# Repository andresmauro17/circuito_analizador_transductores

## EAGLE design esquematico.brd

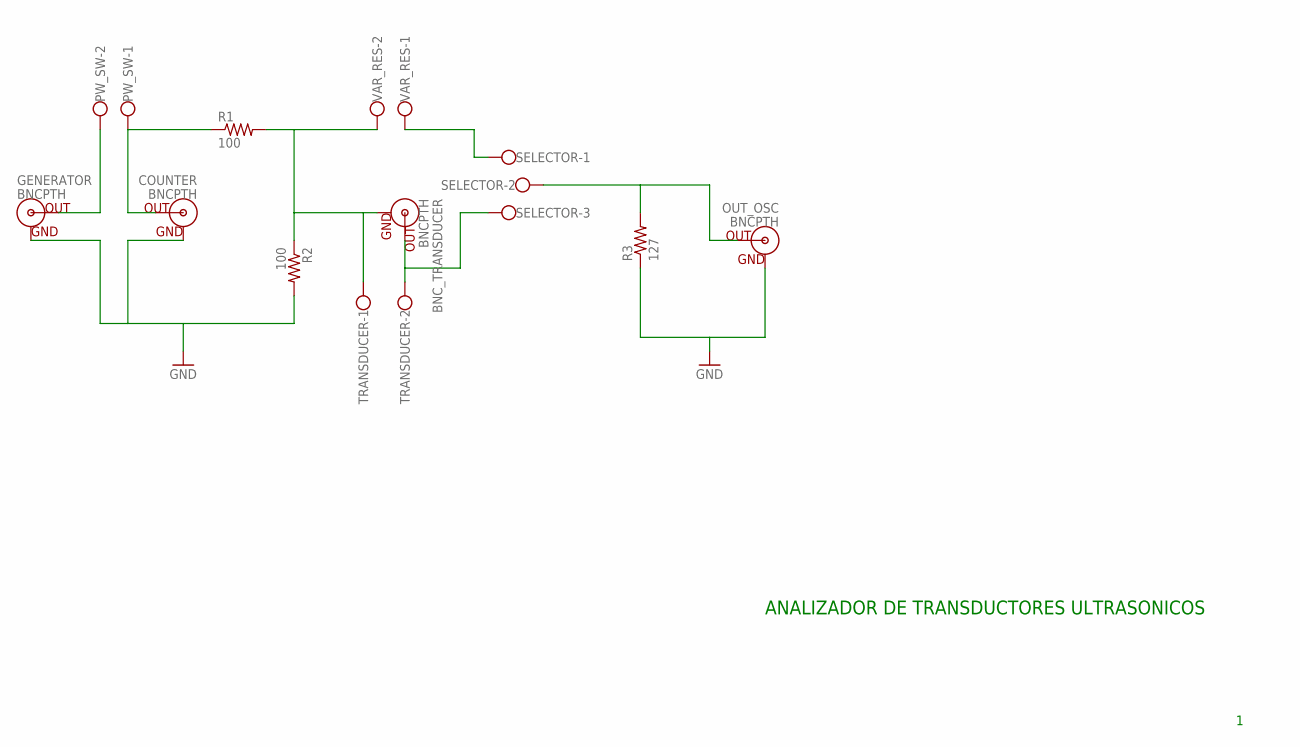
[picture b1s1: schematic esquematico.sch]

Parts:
BNC_TRANSDUCER: BNCPTH; BNC
COUNTER: BNCPTH; BNC
GENERATOR: BNCPTH; BNC
OUT_OSC: BNCPTH; BNC
PW_SW: W237-102
R1, R2: 100; AXIAL-0.4
R3: 127; AXIAL-0.4
SELECTOR: W237-103
TRANSDUCER: W237-102
VAR_RES: W237-102

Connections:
GND: COUNTER.GND, GENERATOR.GND, OUT_OSC.GND, R2.P$2 (2), R3.P$1 (1)
unnamed: BNC_TRANSDUCER.GND, R1.P$2 (2), R2.P$1 (1), TRANSDUCER.1, VAR_RES.2
unnamed: GENERATOR.S (OUT), PW_SW.2
unnamed: COUNTER.S (OUT), PW_SW.1, R1.P$1 (1)
unnamed: BNC_TRANSDUCER.S (OUT), SELECTOR.3, TRANSDUCER.2
unnamed: SELECTOR.1, VAR_RES.1
unnamed: OUT_OSC.S (OUT), R3.P$2 (2), SELECTOR.2

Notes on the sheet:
ANALIZADOR DE TRANSDUCTORES ULTRASONICOS

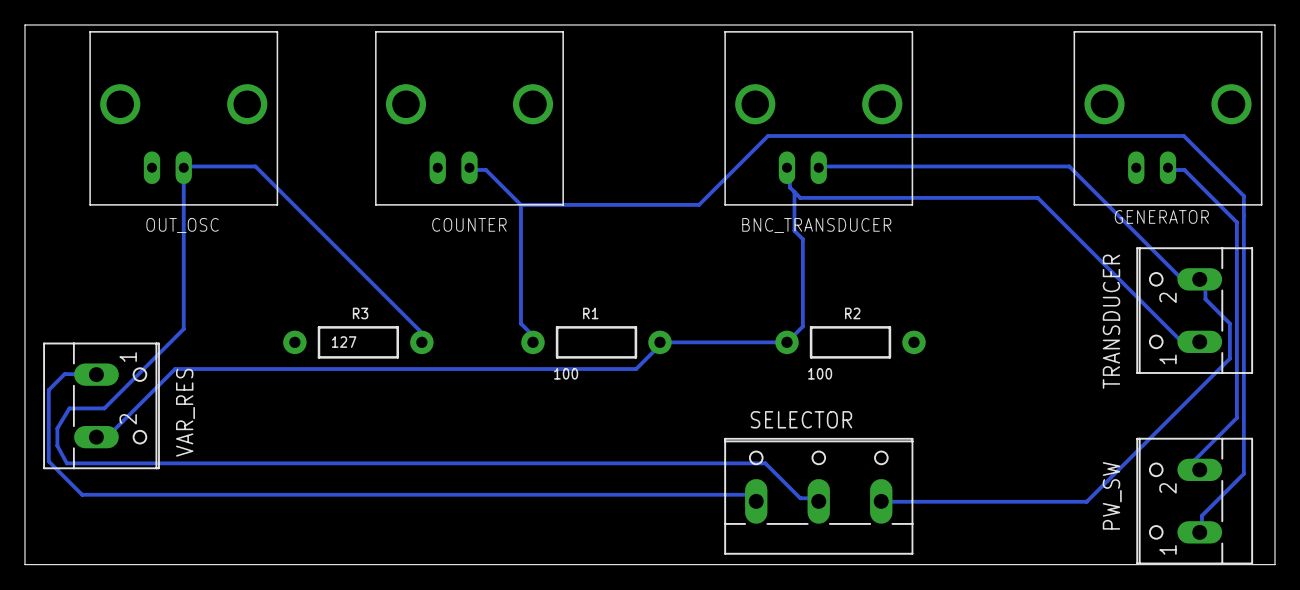
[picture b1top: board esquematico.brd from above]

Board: 2 copper layers, 100.0 x 43.2 mm, 11 parts (0 on the bottom side), 7 nets.

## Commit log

2016-06-24 commit inicial
2016-06-24 commit 2 solo añade el esquematico
2016-07-05 se realiza el primer esschematico
2016-07-05 listo el pcb para el plano de tierra
2016-07-05 anade el plano de tierra
2016-07-05 el proyecto se termina la revision 1.0

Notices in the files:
parts and their libraries:
SparkFun-Connectors: Licensing: Creative Commons ShareAlike 4.0 International - https://creativecommons.org/licenses/by-sa/4.0
